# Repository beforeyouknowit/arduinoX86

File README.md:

### About ArduinoX86

I've written a blog article that gives an overview of this project and how it is used.

https://martypc.blogspot.com/2023/06/hardware-validating-emulator.html

This project was originally called Arduino8088, but then I expanded it to support the 8086, 80186, 80286, with plans for
the 80386, so it is now named the suitably generic ArduinoX86.

### Description

This project expands on the basic idea of controlling a CPU via GPIO pins to clock the CPU and read and write control
and data signals. This can be used to validate an emulator's accuracy, but also as a general method of exploring the
operation of CPU instructions and timings.

This project currently supports the following CPUs:

- CMOS variants of the 8088 (Oki, Harris 80C88, etc.)
- AMD D8088
- CMOS variants of the 8086 (Intel 80C86, Harris 80C86)
- NEC V20
- NEC V30
- Intel 80L186
- Harris 80C286
- Intel 80386EX

Where it differs from existing Raspberry Pi-based projects is that it uses an Arduino Giga for the expanded number of
GPIO pins available. The Giga has enough GPIO to operate 808X-compatible CPUs in Maximum mode. This enables several
useful signals to be read such as the QS0 & QS1 processor instruction queue status lines, which give us more insight
into the internal state of the CPU. We can also enable inputs such as READY, NMI, INTR, and TEST, so we can execute
interrupts, NMIs, emulate wait states, and potentially even simulate FPU and DMA operations.

I have been using this project to validate the cycle-accuracy of my PC
emulator, [MartyPC](https://github.com/dbalsom/martypc), and produce CPU test
suites for emulators, covering
the [8088](https://github.com/singleStepTests/8088/), [V20](https://github.com/SingleStepTests/v20)
and [8086](https://github.com/singleStepTests/8086/) and [286](https://github.com/singlesteptests/80286) to date.

This project has three main components:

- The CPU server software, which runs on the Arduino, and establishes a serial protocol to reset the CPU, load and store
  register state, as well as interactively operate the CPU if desired;
- The CPU client software, which runs on your computer and controls the CPU after the CPU server has set up initial
  register state as desired, or uploads an entire program to be run automatically with register state collected at the
  end of execution;
- The CPU socket PCB shields, which seat on top of the Arduino, and provide a physical interface between the CPU and
  GPIO
  lines.

The original "Arduino8088" project utilized an Arduino MEGA, but this board no longer supported.
It is painfully slow and limited to a serial UART instead of fast native USB communication. As of the current
release, an [Arduino Due](https://store.arduino.cc/products/arduino-due), or preferably,
an [Arduino GIGA](https://store.arduino.cc/products/giga-r1-wifi) should be used instead. A GIGA is required to
operate 5V CPUs such as older 80186's and the 80286. Despite Arduino's official warnings, the STM32 GPIO in the Giga is
5V tolerant (with a few exceptions). You will likely void your warranty and I take no responsibility for any damage to
your Arduino that occurs attempting to use a 5V CPU with your Arduino.

### 8088,8086,V20,V30 Support

Revision 1.1 of the 808X shield supports the 8086 and NEC V30 by adding a connection for the 8086's BHE pin.

The Due can operate the 8088, 8086, V20 and V30, despite these chips being 5V. The current 8088 shield feeds those CPUs
3.3V which they tolerate quite well at low clock speeds.

The Giga can operate the 8088, 8086, V20 and V30 directly at 5V if desired. The Giga requires the 3V supply pin to be
cut off the shield's pin headers and external power supplied due to the lower available overall power budget.

> [!WARNING]  
> Do not attempt to use the 8088 shield with a Giga without using external power, or you may damage your Arduino.

### 80186 Support

The ArduinoX86 cpu_server sketch supports operation of a low-voltage 80L186 on an Arduino Due.

There is no shield yet for the 80186, you will need to use a breakout board and connect directly to the Arduino Due's
headers. See [Using an 80186](https://github.com/dbalsom/arduinoX86/wiki/Using-an-80186) for more information.

### 80286 Support

A shield for the 80C286 is in the design phase, located in `/shields/286_5V`

Current support for the 80286 has been performed via breadboard.

### 80386 Support

A shield for the 80386EX CPU is provided in `/shields/386EX_V4`

## Can the CPU be clocked fast enough with an Arduino?

In short, no. We are well past the published minimum cycle times when executing programs via a serial protocol, cycle by
cycle. Some chips tolerate this better than others. When working with an Intel branded 8088, I noticed that effective
address calculations were failing to add the displacement or index register, but otherwise functioned. I have had more
luck with the AMD second-source 8088 CPUs, which seem to function perfectly under slow clocks, although they will hang
and need to be reset if not cycled for a several milliseconds. The issue is "dynamic logic" - logic gates that lose
their state if not refreshed electrically within a frequent enough interval. To be absolutely safe, it is best to use a
fully CMOS process CPU such as the 80C88. CMOS versions of most x86 chips are available.

## To use

An example application for cpu_server is provided, written in Rust, in the `/crates/exec_program` directory. It
demonstrates how to upload arbitrary code to the ArduinoX86 and display cycle traces. The client will emulate the
entire address space and set up a basic IVT.

# Project Structure

## /asm

Assembly language files, intended to be assembled with NASM. To execute code on the ArduinoX86, one must supply two
binary files, one containing the program to be executed, and one containing the register values to load onto the CPU
before program execution.

## /crates/arduinox86_client

A library crate that implements a client for the ArduinoX86's serial protocol.

## /crates/arduinox86_cpu

A library crate built on top of the `arduinox86_client` crate, this provides a `RemoteCpu` struct that models CPU state
and can execute programs.

## /crates/arduinox86_gui

A GUI (written in egui) for ArduinoX86, supporting the 386EX. It allows you to write and assemble assembly-language
programs and execute them on the CPU with an easy-to-use interface.

## /crates/exec_program

A binary implementing an interface for the `arduinox86_cpu` crate that will load a provided register state binary and
execute the specified program binary.

## /crates/test_generator

A program that generates CPU tests for emulator authors.

### /shields

Contains the KiCad project files and Gerber files for the various ArduinoX86 shields. See the README.md in each shield
directory for more information and BOMs for building each.

### /platformio/ArduinoX86

The main server code that runs on the Arduino Due or GIGA. You must have [platformio](https://platformio.org/) installed
to build and upload the project to your Arduino.

## Archived Directories

### /sketches/cpu_server

The original cpu_server Arduino IDE sketch. Development has since moved to platformio.

### /sketches/run_program

The original sketch for Arduino MEGA only demonstrating how to control an 8088. It does not contain a serial protocol
server - code is run directly from an array defined within the sketch.

# Ordering Boards

- Ordering boards from any of the KiCad projects is extremely simple using PCBWay's KiCad fabrication plugin.
  - From the Plugin and Content Manager, go the Fabrication Plugins tab, find the PCBWay plugin and install.
  - 
  - Open the PCB editor and click the PCBWay Button
  - 
  - A browser window will open to PCBWay's website with the project uploaded and acceptable defaults selected.
  - If you like you can change the board color, or get a nicer finish with gold (ENIG).
  - 
  - You can then proceed to ordering. Part of your purchase goes back to help fund the KiCad project, which is cool.
  - 

# Credits

Inspired by the Pi8088 validator created by Andreas Jonsson as part of the VirtualXT project:

https://github.com/andreas-jonsson/virtualxt/tree/develop/tools/validator/pi8088

# Other Cool Projects

- 8bitforce's Retroshield: https://www.8bitforce.com/projects/retroshield/

- homebrew8088's Raspberry Pi Hat: https://github.com/homebrew8088/pi86

- The Universal Chip Analyser (U. C. A.): https://x86.fr/uca/

- Foxtech's 486 Breadboard Computer: https://www.youtube.com/watch?v=wSiDSdHS2QQ

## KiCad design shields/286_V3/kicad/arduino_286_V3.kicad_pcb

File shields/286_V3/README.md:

## ArduinoX86 286 5V Shield

This Shield is for a 5V CMOS 286 in a PLCC-68 package, such as the Harris 80C286.

> [!WARNING]  
> This hat is to be used ONLY with the Arduino GIGA. Using this HAT with an Arduino Due will damage/destroy your
> Arduino.

> [!CAUTION]
> This hat is in development. Do not order it.

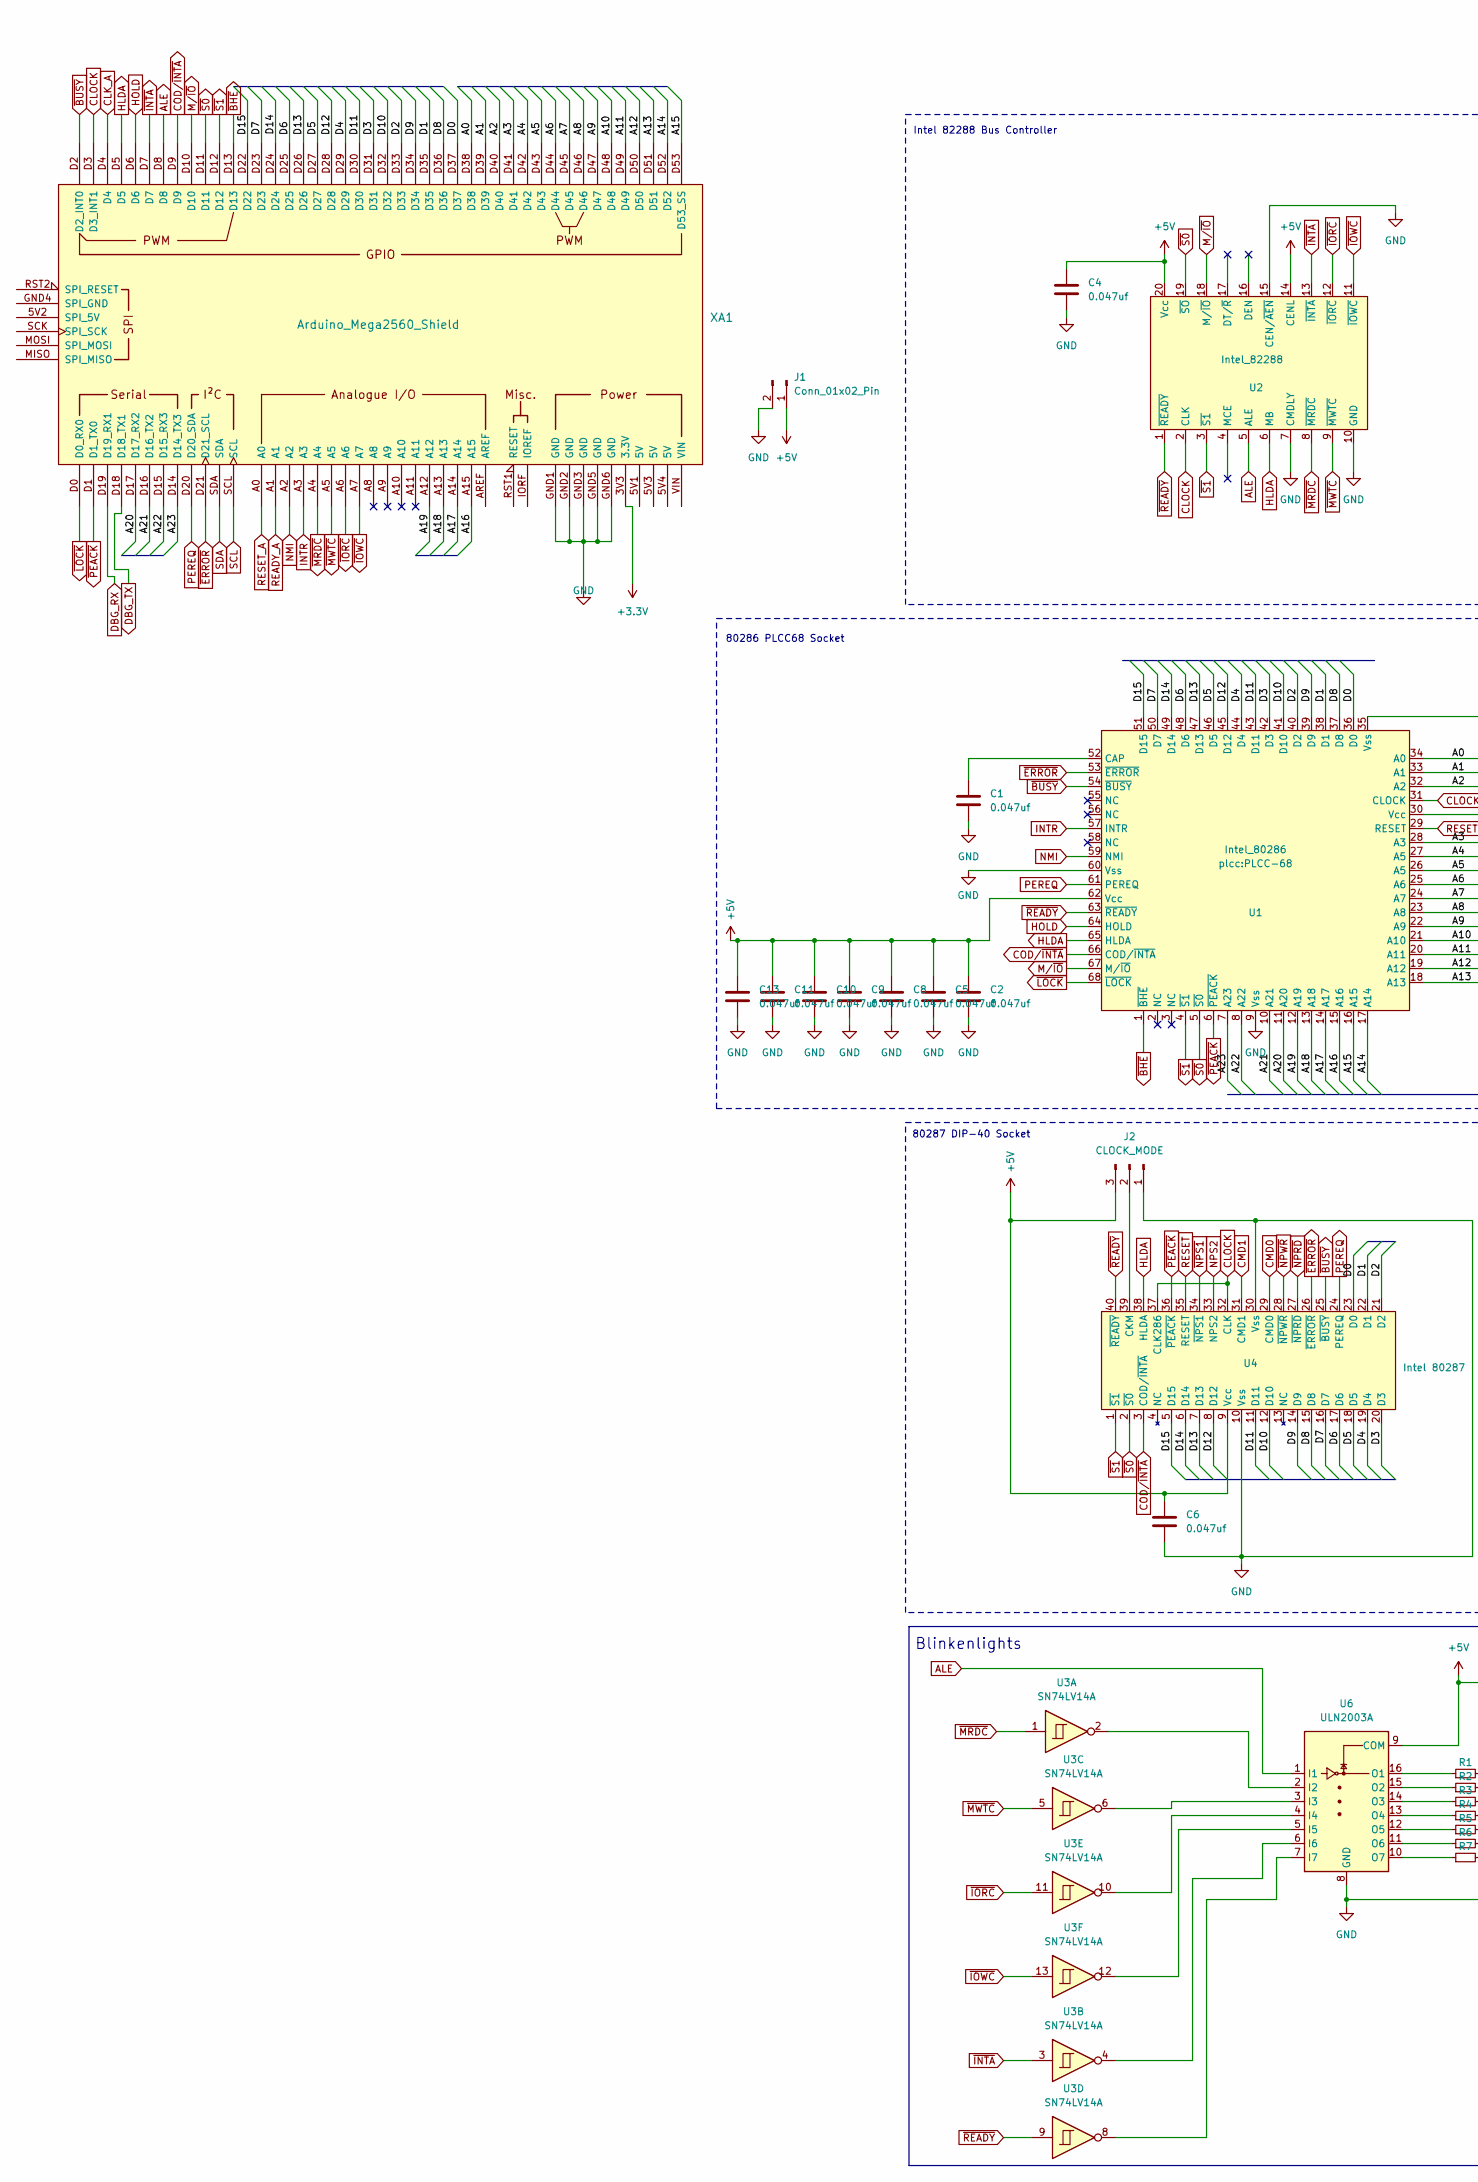
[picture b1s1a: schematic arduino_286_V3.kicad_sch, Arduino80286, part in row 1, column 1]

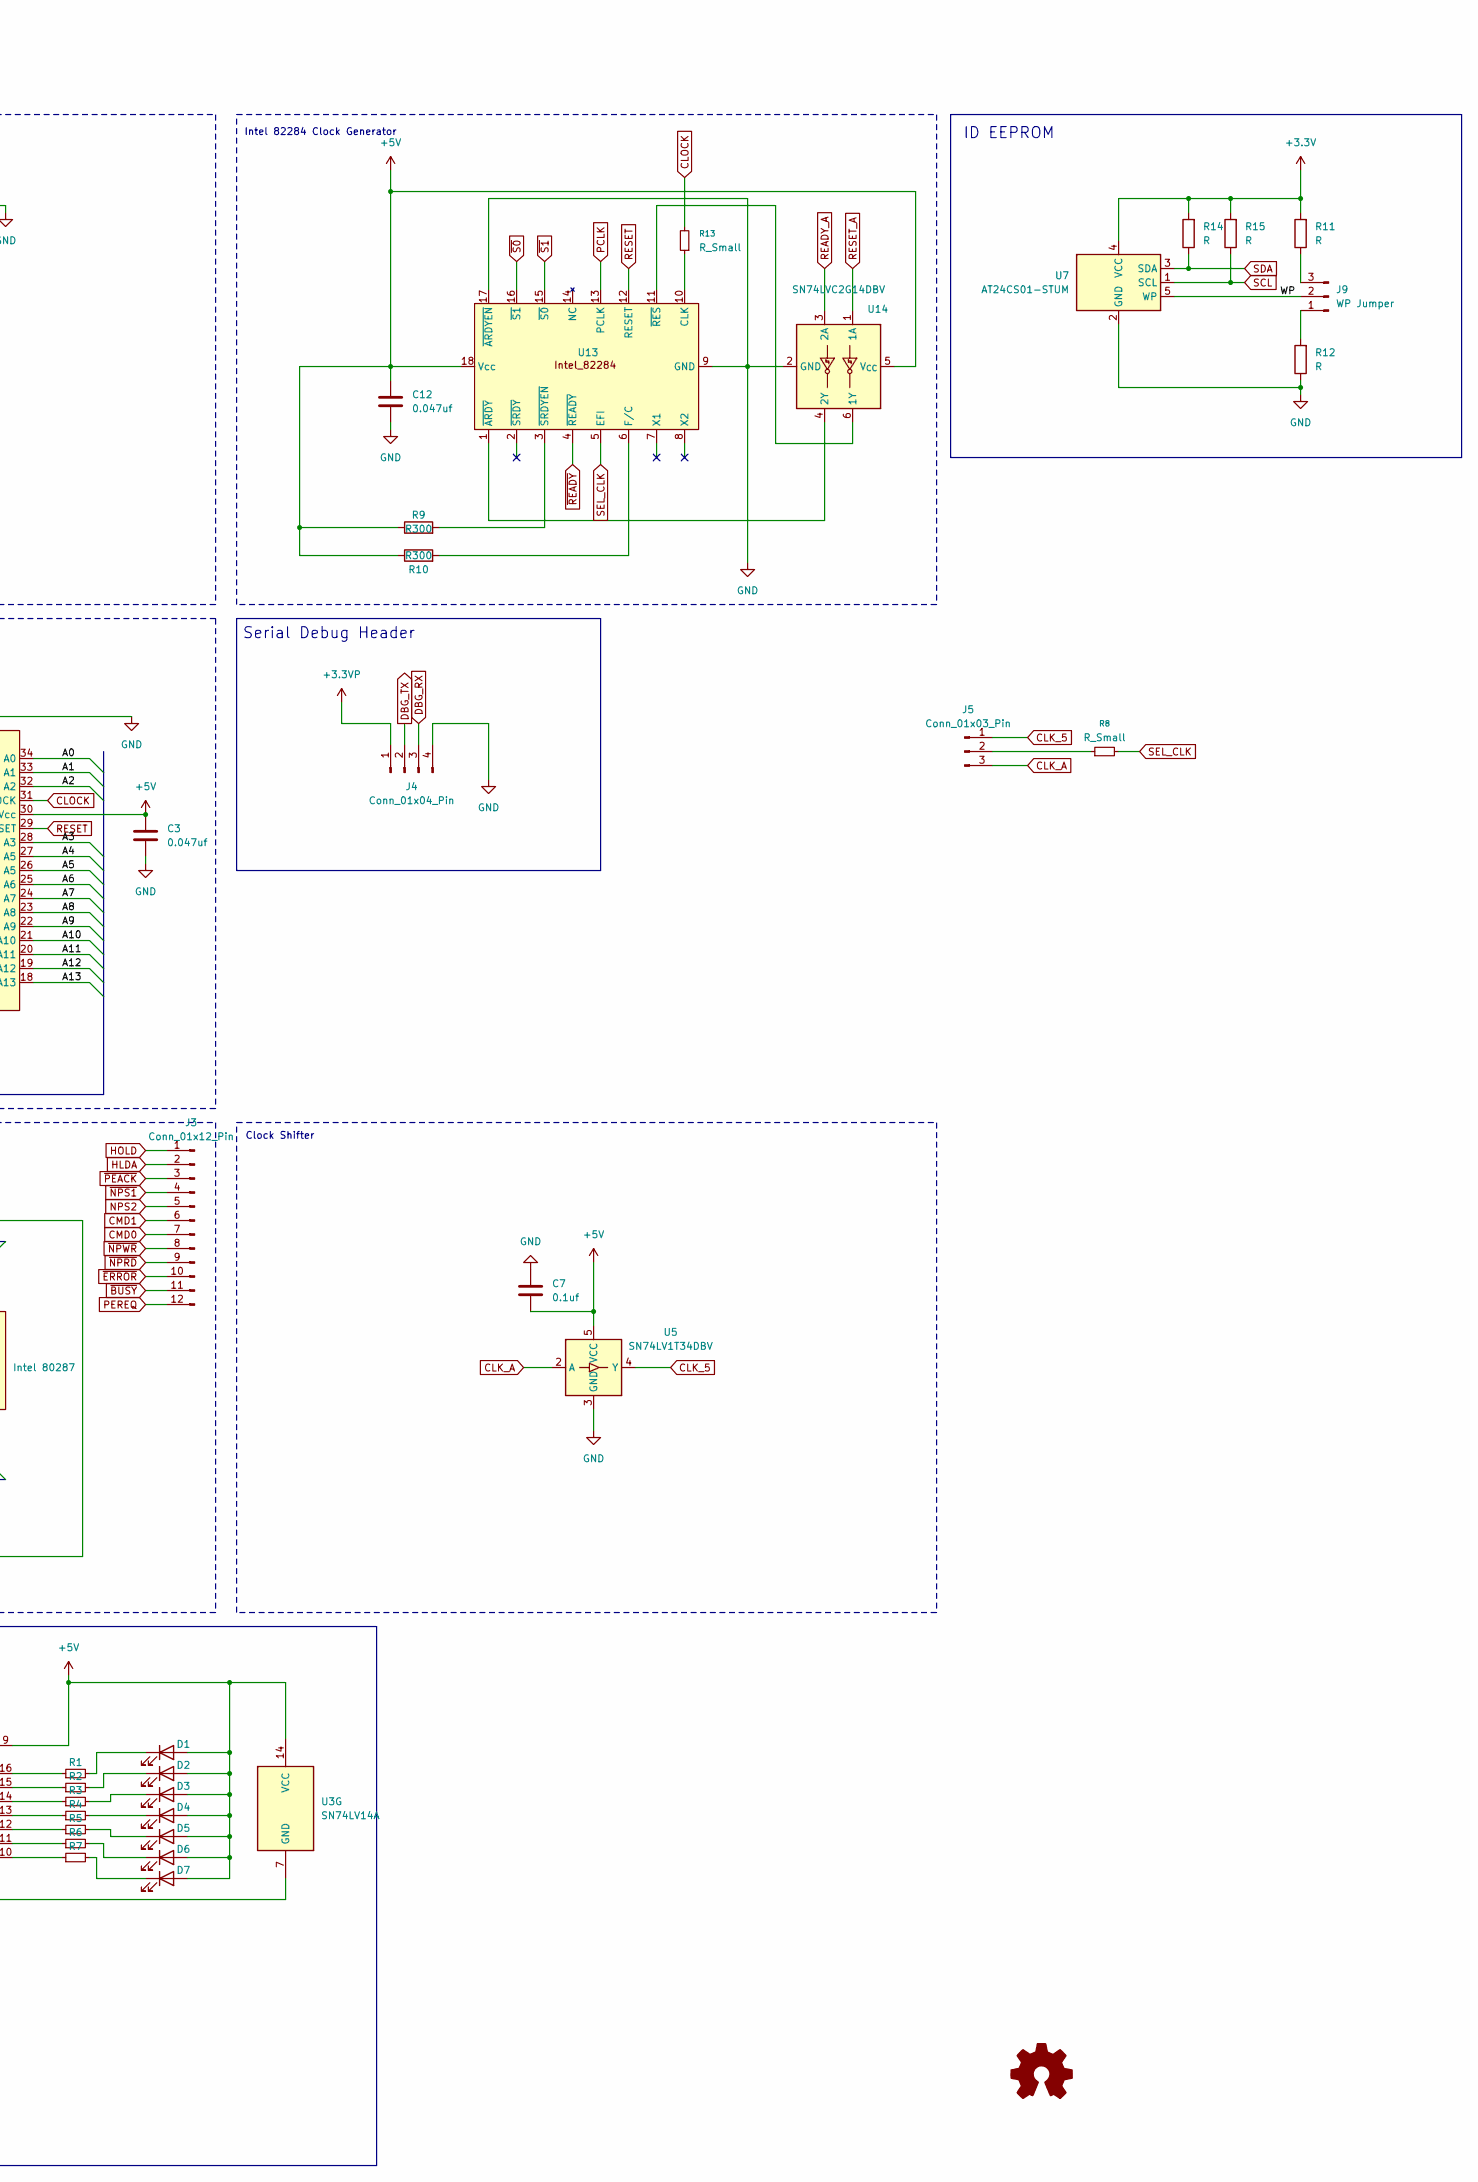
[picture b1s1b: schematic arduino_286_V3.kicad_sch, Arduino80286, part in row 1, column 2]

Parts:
C1, C2, C3, C4, C5, C6, C8, C9, C10, C11, C12, C13: 0.047uf; C_0603_1608Metric_Pad1.08x0.95mm_HandSolder
C7: 0.1uf; C_0603_1608Metric_Pad1.08x0.95mm_HandSolder
D1, D2, D3, D4, D5, D6, D7: LED; LED_0603_1608Metric_Pad1.05x0.95mm_HandSolder
J1: Conn_01x02_Pin; PinHeader_1x02_P2.54mm_Horizontal
J2: CLOCK_MODE; PinHeader_1x03_P2.54mm_Vertical
J3: Conn_01x12_Pin; PinHeader_1x12_P2.54mm_Vertical
J4: Conn_01x04_Pin; PinHeader_1x04_P2.54mm_Vertical
J5: Conn_01x03_Pin; PinHeader_1x03_P2.54mm_Vertical
J9: WP Jumper; PinHeader_1x03_P2.54mm_Vertical
R1, R2, R3, R4, R5, R6, R7, R8, R13: R_Small; R_0603_1608Metric_Pad0.98x0.95mm_HandSolder
R9, R10: R300; R_0603_1608Metric_Pad0.98x0.95mm_HandSolder
R11, R12, R14, R15: R; R_0603_1608Metric_Pad0.98x0.95mm_HandSolder
U1: Intel_80286; PLCC-68
U2: Intel_82288; DIP-20_W7.62mm_Socket
U3: SN74LV14A; TSSOP-14_4.4x5mm_P0.65mm
U4: Intel 80287; DIP-40_W15.24mm_Socket
U5: SN74LV1T34DBV; SOT-23-5
U6: ULN2003A; TSSOP-16_4.4x5mm_P0.65mm
U7: AT24CS01-STUM; SOT-23-5
U13: DIP-18_W7.62mm_Socket
U14: SN74LVC2G14DBV; SOT-23-6
XA1: Arduino_Mega2560_Shield

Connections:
+3.3V: R11.2, R14.2, R15.2, U7.4 (VCC), XA1.3V3 (3.3V); also elsewhere on the board
+3.3VP: J4.1
/A0: U1.34 (A0), XA1.D38
/A1: U1.33 (A1), XA1.D39
/A2: U1.32 (A2), XA1.D40
/A3: U1.28 (A3), XA1.D41
/A4: U1.27 (A5), XA1.D42
/A5: U1.26 (A5), XA1.D43
/A6: U1.25 (A6), XA1.D44
/A7: U1.24 (A7), XA1.D45
/A8: U1.23 (A8), XA1.D46
/A9: U1.22 (A9), XA1.D47
/A10: U1.21 (A10), XA1.D48
/A11: U1.20 (A11), XA1.D49
/A12: U1.19 (A12), XA1.D50
/A13: U1.18 (A13), XA1.D51
/A14: U1.17 (A14), XA1.D52
/A15: U1.16 (A15), XA1.D53 (D53_SS)
/A16: U1.15 (A16), XA1.A15
/A17: U1.14 (A17), XA1.A14
/A18: U1.13 (A18), XA1.A13
/A19: U1.12 (A19), XA1.A12
/A20: U1.11 (A20), XA1.D17 (D17_RX2)
/A21: U1.10 (A21), XA1.D16 (D16_TX2)
/A22: U1.8 (A22), XA1.D15 (D15_RX3)
/A23: U1.7 (A23), XA1.D14 (D14_TX3)
/D0: U1.36 (D0), U4.23 (D0), XA1.D37
/D1: U1.38 (D1), U4.22 (D1), XA1.D35
/D2: U1.40 (D2), U4.21 (D2), XA1.D33
/D3: U1.42 (D3), U4.20 (D3), XA1.D31
/D4: U1.44 (D4), U4.19 (D4), XA1.D29
/D5: U1.46 (D5), U4.18 (D5), XA1.D27
/D6: U1.48 (D6), U4.17 (D6), XA1.D25
/D7: U1.50 (D7), U4.16 (D7), XA1.D23
/D8: U1.37 (D8), U4.15 (D8), XA1.D36
/D9: U1.39 (D9), U4.14 (D9), XA1.D34
/D10: U1.41 (D10), U4.12 (D10), XA1.D32
/D11: U1.43 (D11), U4.11 (D11), XA1.D30
/D12: U1.45 (D12), U4.8 (D12), XA1.D28
/D13: U1.47 (D13), U4.7 (D13), XA1.D26
/D14: U1.49 (D14), U4.6 (D14), XA1.D24
/D15: U1.51 (D15), U4.5 (D15), XA1.D22
/WP: J9.2, U7.5 (WP)
ALE: U2.5 (ALE), U6.1 (I1), XA1.D8
CLK_5: J5.1, U5.4 (Y)
CLK_A: J5.3, U5.2 (A), XA1.D4
CLOCK: R13.2, U1.31 (CLOCK), U2.2 (CLK), U4.32 (CLK), U4.37 (CLK286), XA1.D3 (D3_INT1)
COD/~INTA: U1.66 (COD/~INTA), U4.3 (COD/~INTA), XA1.D9
DBG_RX: J4.3, XA1.D19 (D19_RX1)
DBG_TX: J4.2, XA1.D18 (D18_TX1)
HLDA: J3.2, U1.65 (HLDA), U2.6 (MB), U4.38 (HLDA), XA1.D5
HOLD: J3.1, U1.64 (HOLD), XA1.D6
INTR: U1.57 (INTR), XA1.A3
M/~IO: U1.67 (M/~IO), U2.18 (M/~IO), XA1.D10
NMI: U1.59 (NMI), XA1.A2
unnamed: D1.1 (K), R1.2
unnamed: D2.1 (K), R2.2
unnamed: D3.1 (K), R3.2
unnamed: D4.1 (K), R4.2
unnamed: D5.1 (K), R5.2
unnamed: D7.1 (K), R7.2
unnamed: J2.2, U4.39 (CKM)
unnamed: J3.4, U4.34 (~NPS1)
unnamed: J3.5, U4.33 (NPS2)
unnamed: J3.6, U4.31 (CMD1)
unnamed: J3.7, U4.29 (CMD0)
unnamed: J3.8, U4.28 (~NPWR)
unnamed: J3.9, U4.27 (~NPRD)
unnamed: J5.2, R8.1
unnamed: J9.1, R12.2
unnamed: J9.3, R11.1
unnamed: C1.2, U1.52 (CAP)
unnamed: U3.2, U6.2 (I2)
unnamed: U3.6, U6.3 (I3)
unnamed: U3.10, U6.4 (I4)
unnamed: U3.12, U6.5 (I5)
unnamed: U3.4, U6.6 (I6)
unnamed: U3.8, U6.7 (I7)
unnamed: R1.1, U6.16 (O1)
unnamed: R2.1, U6.15 (O2)
unnamed: R3.1, U6.14 (O3)
unnamed: R4.1, U6.13 (O4)
unnamed: R5.1, U6.12 (O5)
unnamed: R6.1, U6.11 (O6)
unnamed: R7.1, U6.10 (O7)
unnamed: R13.1, U13.10 (CLK)
unnamed: R10.2, U13.6 (F/C)
unnamed: U13.1 (~ARDY), U14.4 (2Y)
unnamed: U13.11 (~RES), U14.6 (1Y)
unnamed: R9.2, U13.3 (~SRDYEN)
PCLK: U13.13 (PCLK)
PEREQ: J3.12, U1.61 (PEREQ), U4.24 (PEREQ), XA1.D20 (D20_SDA)
READY_A: U14.3 (2A), XA1.A1
RESET: U1.29 (RESET), U4.35 (RESET), U13.12 (RESET)
RESET_A: U14.1 (1A), XA1.A0
SCL: R15.1, U7.1 (SCL), XA1.SCL
SDA: R14.1, U7.3 (SDA), XA1.SDA
SEL_CLK: R8.2, U13.5 (EFI)
~BHE: U1.1 (~BHE), XA1.D13
~BUSY: J3.11, U1.54 (~BUSY), U4.25 (~BUSY), XA1.D2 (D2_INT0)
~ERROR: J3.10, U1.53 (~ERROR), U4.26 (~ERROR), XA1.D21 (D21_SCL)
~INTA: U2.13 (~INTA), U3.3, XA1.D7
~IORC: U2.12 (~IORC), U3.11, XA1.A6
~IOWC: U2.11 (~IOWC), U3.13, XA1.A7
~LOCK: U1.68 (~LOCK), XA1.D0 (D0_RX0)
~MRDC: U2.8 (~MRDC), U3.1, XA1.A4
~MWTC: U2.9 (~MWTC), U3.5, XA1.A5
~PEACK: J3.3, U1.6 (~PEACK), U4.36 (~PEACK), XA1.D1 (D1_TX0)
~READY: U1.63 (~READY), U2.1 (~READY), U3.9, U4.40 (~READY), U13.4 (~READY)
~S0: U1.5 (~S0), U2.19 (~SO), U4.2 (~S0), U13.16 (~S1), XA1.D11
~S1: U1.4 (~S1), U2.3 (~S1), U4.1 (~S1), U13.15 (~S0), XA1.D12

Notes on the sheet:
Blinkenlights
ID EEPROM
Intel 82284 Clock Generator
Clock Shifter
Intel 82288 Bus Controller
80286 PLCC68 Socket
80287 DIP-40 Socket
Serial Debug Header

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
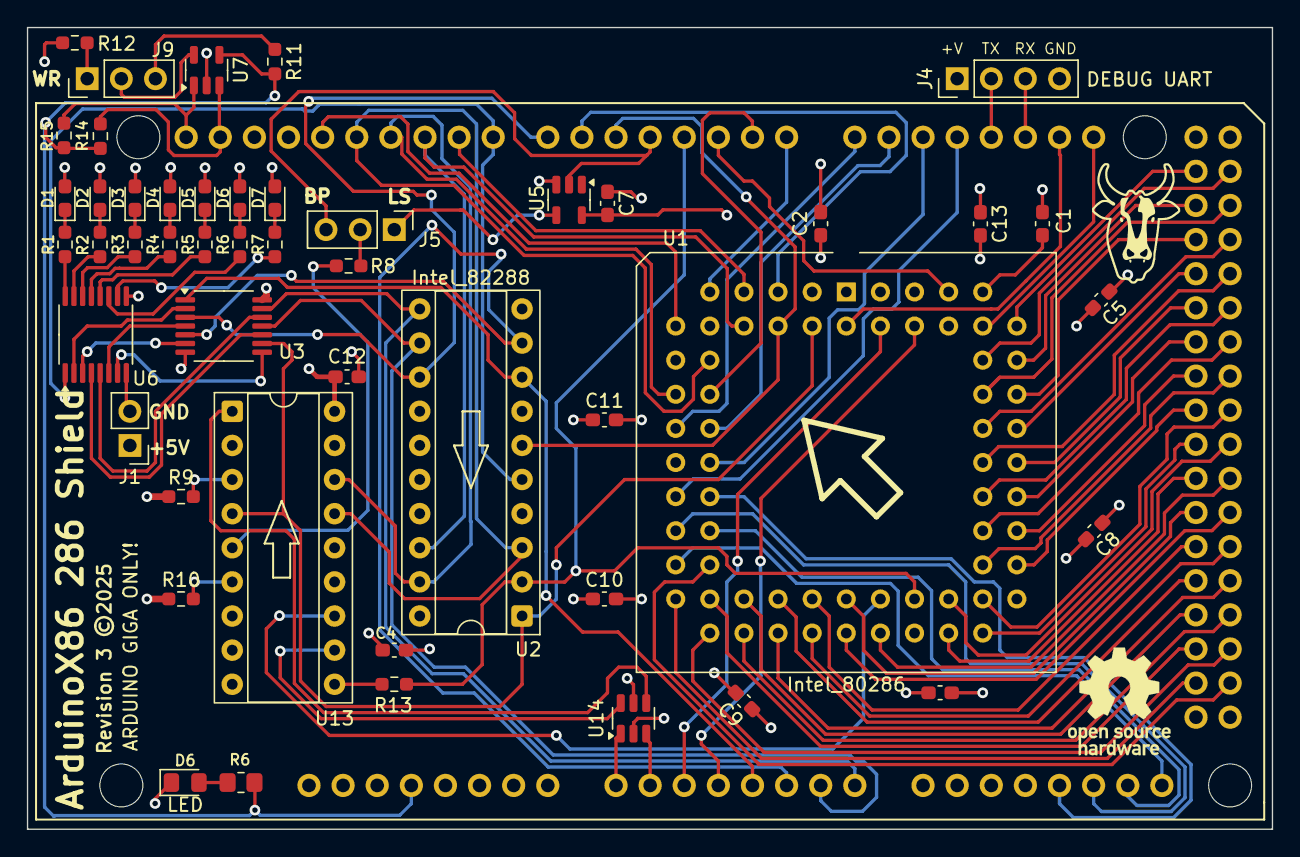
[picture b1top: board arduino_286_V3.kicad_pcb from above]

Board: 4 copper layers, 92.7 x 59.7 mm, 49 parts (0 on the bottom side), 106 nets.

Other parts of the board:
D6#2: LED; LED_0603_1608Metric_Pad1.05x0.95mm_HandSolder
R6#2: 750Ω; R_0805_2012Metric_Pad1.20x1.40mm_HandSolder

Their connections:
+3.3V: R6#2.1; also elsewhere on the board

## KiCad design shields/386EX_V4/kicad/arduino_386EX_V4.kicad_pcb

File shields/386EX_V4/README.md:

## ArduinoX86 386EX Shield V4

This is the latest shield design for the 386EX CPU. It supports the addition of a 387SX FPU via stacking headers.
The 386EX is a low-voltage variant of the 386 with a 16-bit data bus, intended for embedded applications.

This shield has external power pins. You may connect a 3.3V or 5V power source to the pins. I recommend using Dupont
connectors.

You may find that the CPU runs even without external power. This is due to the CMOS process - many CMOS CPUs can power
themselves by sinking current from any input pin. Correct operation in this state is not guaranteed.

This shield should be compatible with the Arduino Due and GIGA. If using a Due, do not supply more than 3.3V to the
external power pins, or you will damage your Arduino Due.

Unsoldered new-old-stock 386EX chips are often available on eBay. If using a donor board, a hot plate or hot-air
station will be necessary to successfully remove the CPU without damage.

This shield adds new features over the original:

- PEREQ and ERROR pins have been connected to support stacking a 387SX
- The SMI and SMIACT pins have been connected
- The JTAG ports have been run out to a 2x4 header
- The first Asynchronous serial port has been run out to a 2x5 header (Serial0)
- The first 8 external INTR lines (INTR0-INTR7) have been run out to separate 1x4 headers
- 7 status LEDs have been added that will report the status of SMIACT, ADS, RD, WR, W/R, C/M and M/IO.

Improvements over the previous design include:

- Series termination resistor on the clock line
- Optional filter caps on the external power connector
- Larger Schmitt-triggered inverter chip to invert the D/C and M/IO LED logic states
- Test probe pads for the clock line near the CPU
- I2C EEPROM for automatic board identification and write-protect jumper

> [!WARNING]  
> Successfully assembling this board requires advanced soldering skills. A solder mask, paste and hot plate are
> recommended, or solid experience in drag-soldering techniques.

## BOM

- TBD

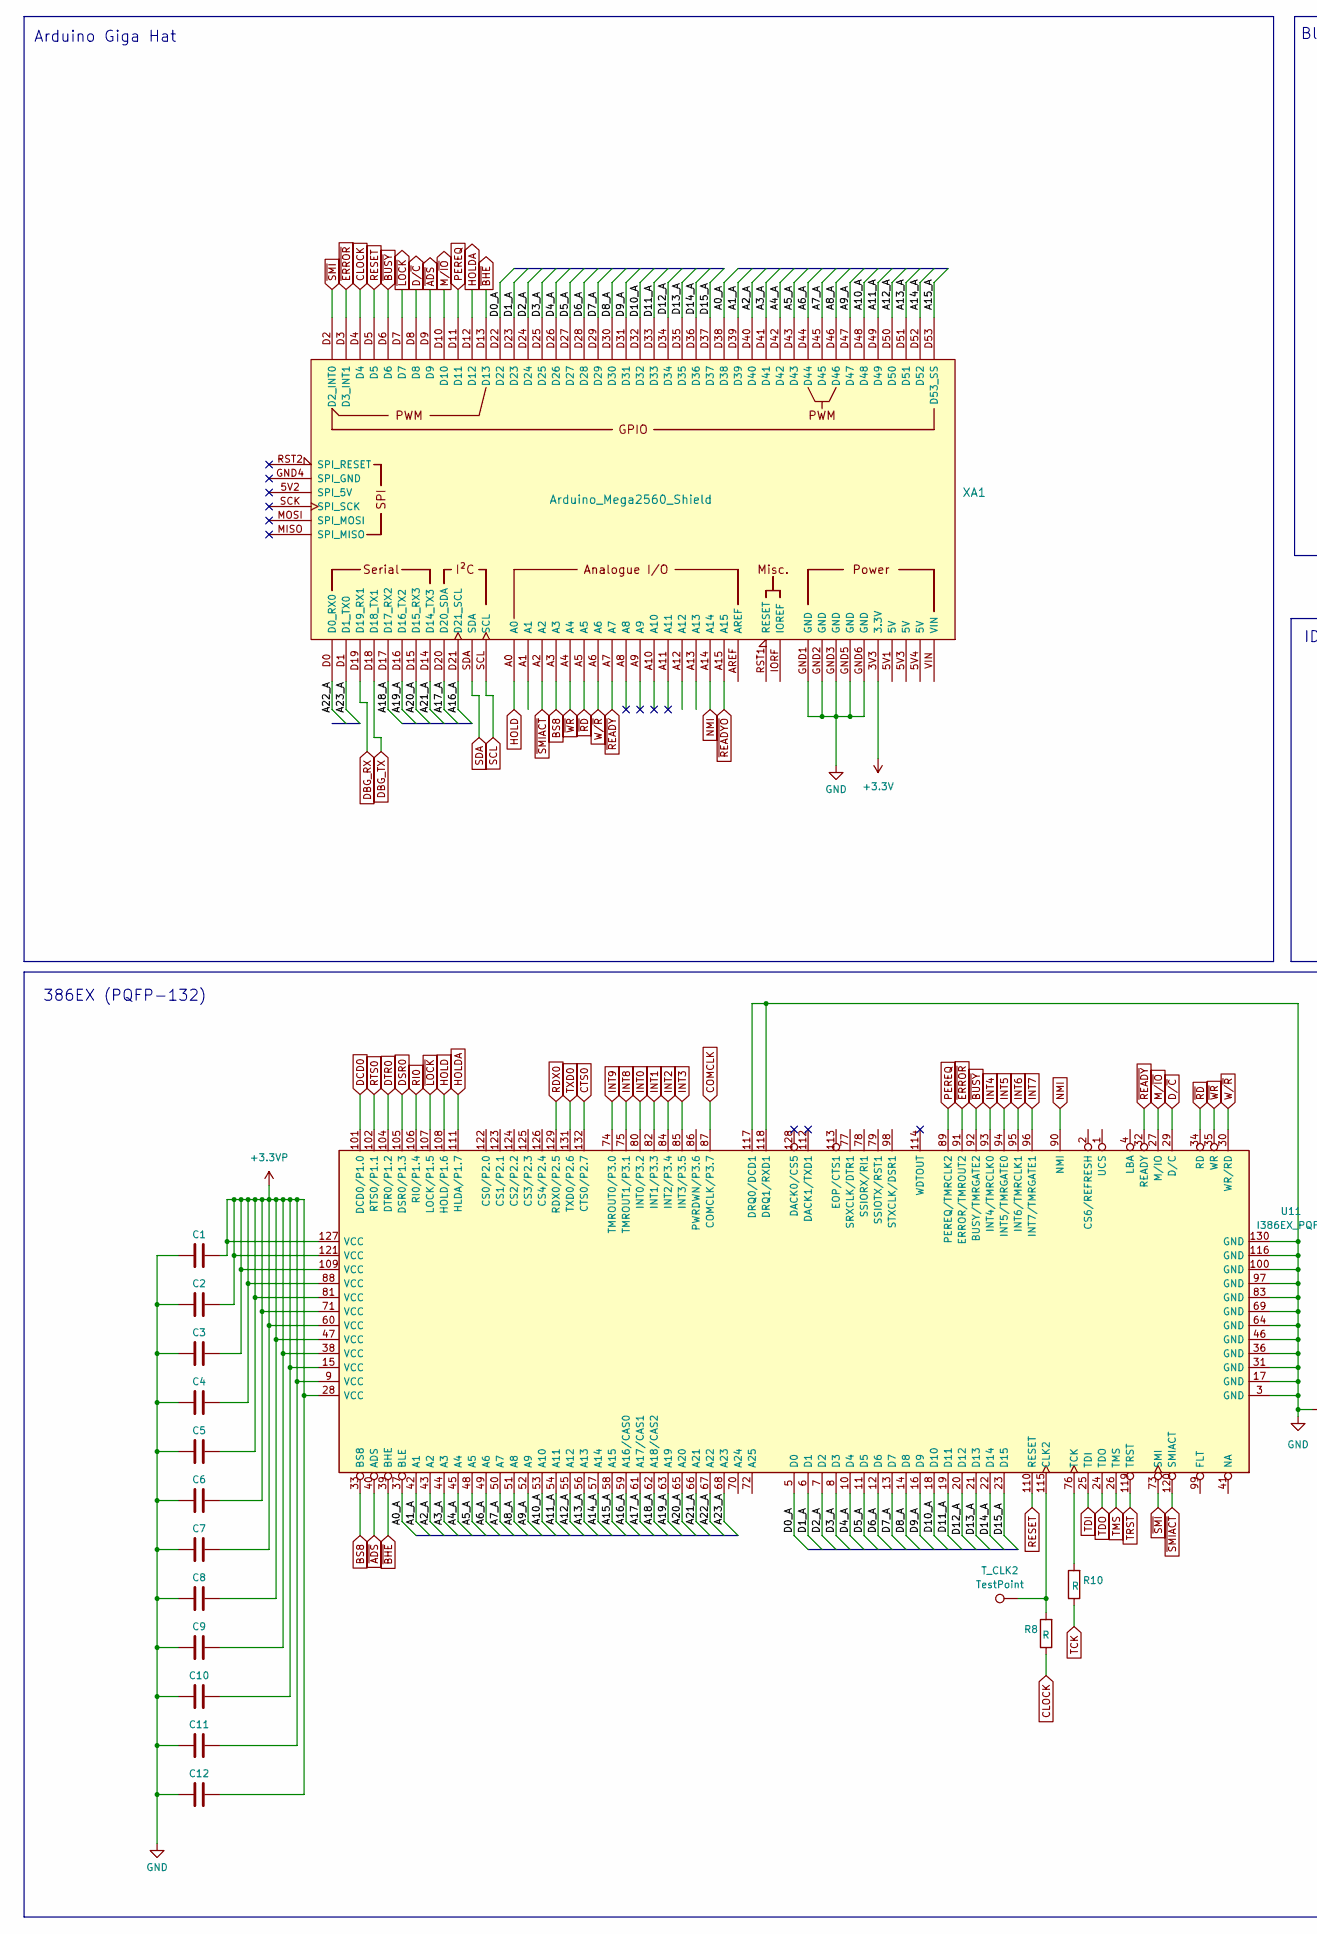
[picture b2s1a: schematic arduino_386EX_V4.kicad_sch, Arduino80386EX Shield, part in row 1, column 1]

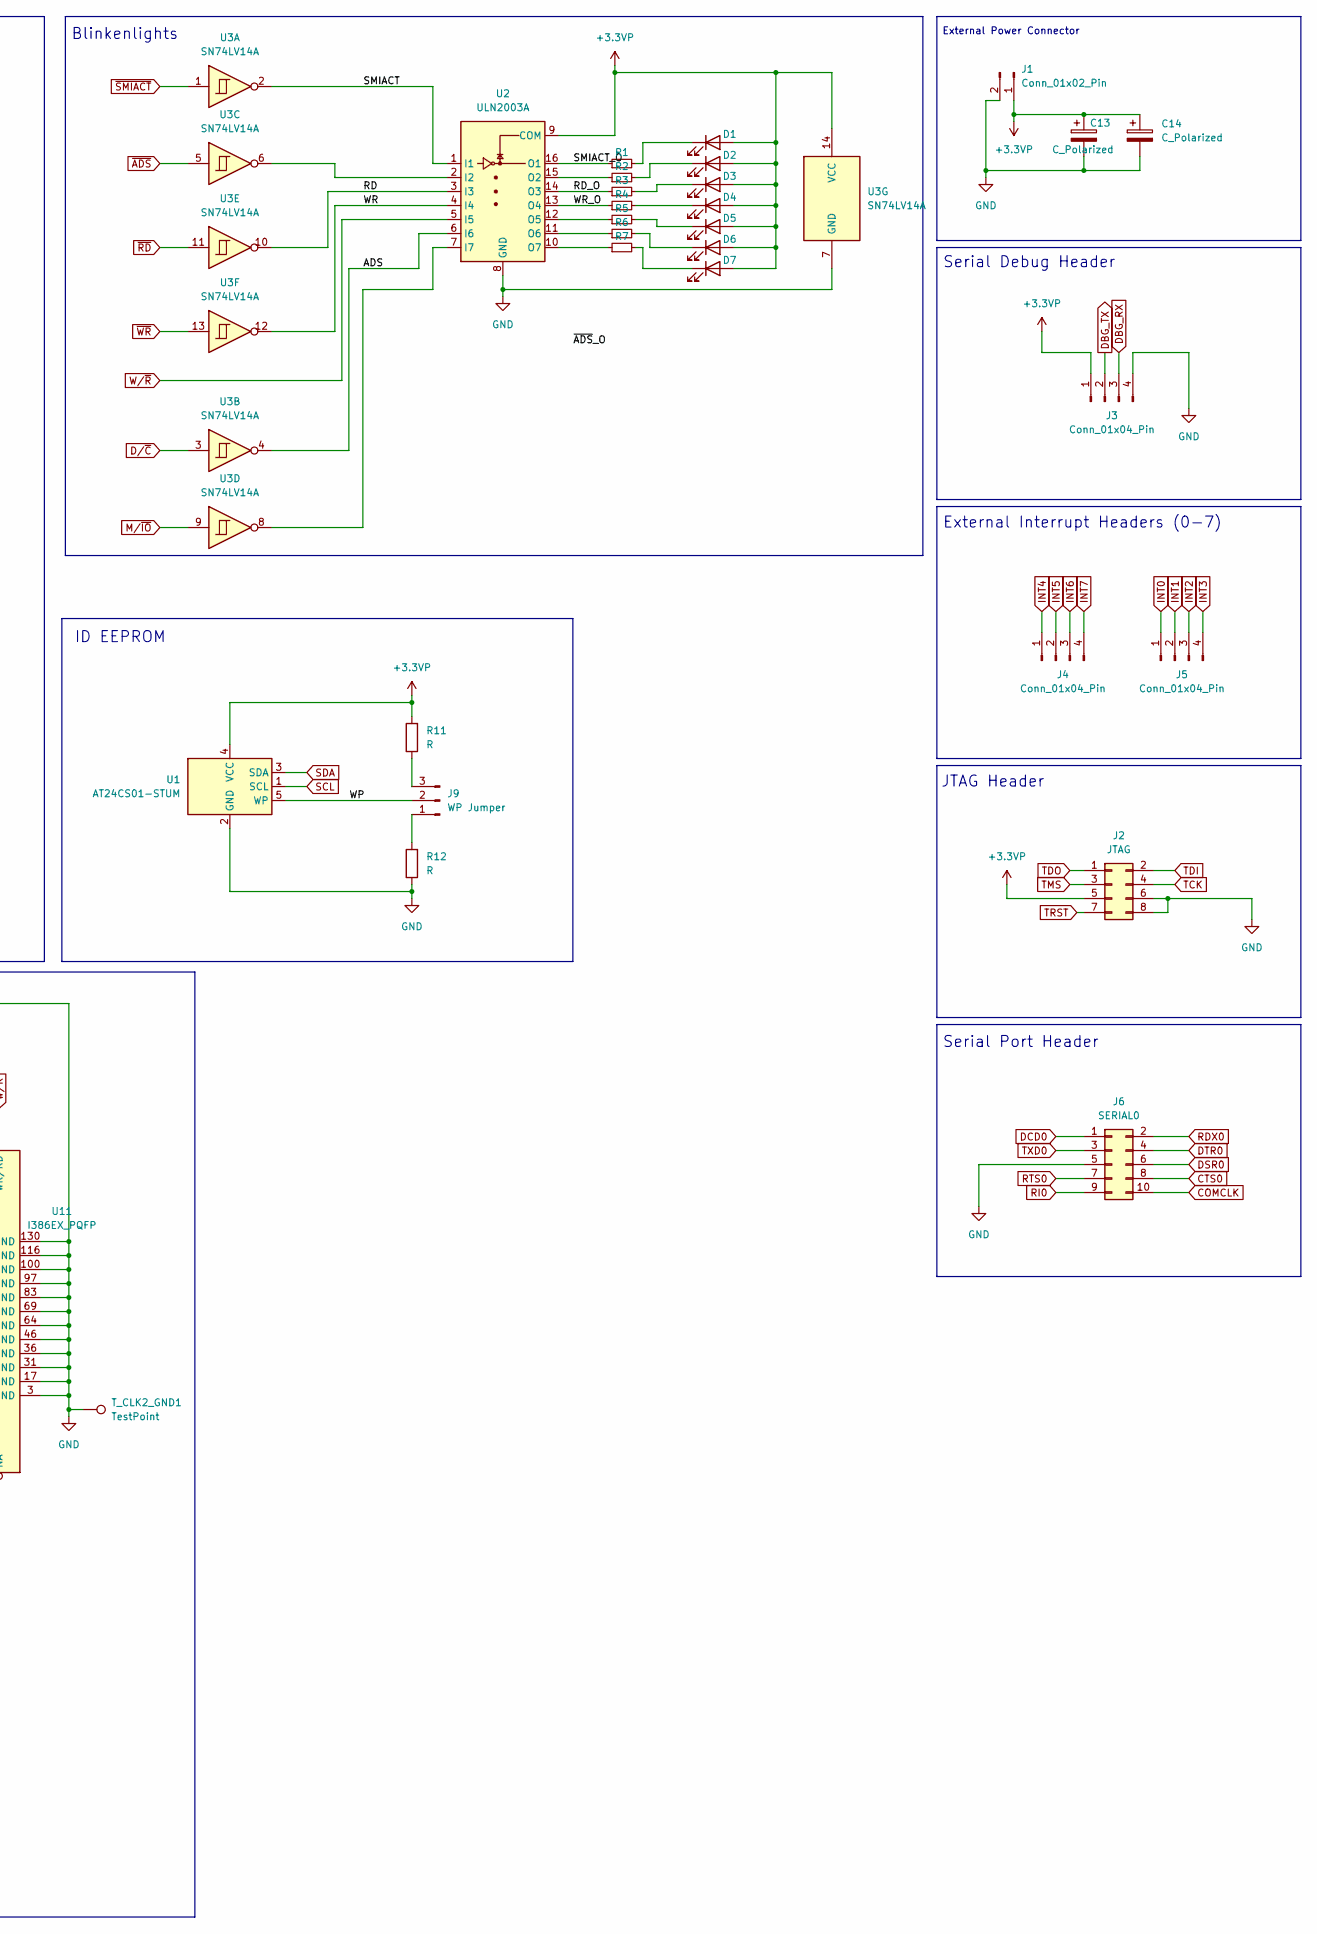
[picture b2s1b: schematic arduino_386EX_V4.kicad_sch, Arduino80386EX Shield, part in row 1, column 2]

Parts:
C1, C2, C3, C4, C5, C6, C7, C8, C9, C10, C11, C12: C; C_0603_1608Metric_Pad1.08x0.95mm_HandSolder
C13: C_Polarized; C_Radial_D4.0mm_H5.0mm_P1.50mm
C14: C_Polarized; C_Disc_D5.0mm_W2.5mm_P2.50mm
D1, D2, D3, D4, D5, D6, D7: LED; LED_0603_1608Metric_Pad1.05x0.95mm_HandSolder
J1: Conn_01x02_Pin; PinHeader_1x02_P2.54mm_Horizontal
J2: JTAG; PinHeader_2x04_P2.54mm_Vertical
J3, J4, J5: Conn_01x04_Pin; PinHeader_1x04_P2.54mm_Vertical
J6: SERIAL0; PinHeader_2x05_P2.54mm_Vertical
J9: WP Jumper; PinHeader_1x03_P2.54mm_Vertical
R1, R2, R3, R4, R5, R6, R7: R_Small; R_0603_1608Metric_Pad0.98x0.95mm_HandSolder
R8, R10, R11, R12: R; R_0603_1608Metric_Pad0.98x0.95mm_HandSolder
T_CLK2, T_CLK2_GND1: TestPoint; TestPoint_Pad_D1.0mm
U1: AT24CS01-STUM; SOT-23-5
U2: ULN2003A; TSSOP-16_4.4x5mm_P0.65mm
U3: SN74LV14A; TSSOP-14_4.4x5mm_P0.65mm
U11: I386EX_PQFP; PQFP-132_24x24mm_P0.635mm_i386
XA1: Arduino_Mega2560_Shield

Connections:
/A0_A: U11.37 (BLE), XA1.D38
/A1_A: U11.42 (A1), XA1.D39
/A2_A: U11.43 (A2), XA1.D40
/A3_A: U11.44 (A3), XA1.D41
/A4_A: U11.45 (A4), XA1.D42
/A5_A: U11.48 (A5), XA1.D43
/A6_A: U11.49 (A6), XA1.D44
/A7_A: U11.50 (A7), XA1.D45
/A8_A: U11.51 (A8), XA1.D46
/A9_A: U11.52 (A9), XA1.D47
/A10_A: U11.53 (A10), XA1.D48
/A11_A: U11.54 (A11), XA1.D49
/A12_A: U11.55 (A12), XA1.D50
/A13_A: U11.56 (A13), XA1.D51
/A14_A: U11.57 (A14), XA1.D52
/A15_A: U11.58 (A15), XA1.D53 (D53_SS)
/A16_A: U11.59 (A16/CAS0), XA1.D21 (D21_SCL)
/A17_A: U11.61 (A17/CAS1), XA1.D20 (D20_SDA)
/A18_A: U11.62 (A18/CAS2), XA1.D17 (D17_RX2)
/A19_A: U11.63 (A19), XA1.D16 (D16_TX2)
/A20_A: U11.65 (A20), XA1.D15 (D15_RX3)
/A21_A: U11.66 (A21), XA1.D14 (D14_TX3)
/A22_A: U11.67 (A22), XA1.D0 (D0_RX0)
/A23_A: U11.68 (A23), XA1.D1 (D1_TX0)
/ADS: U2.6 (I6), U3.4
/D0_A: U11.5 (D0), XA1.D22
/D1_A: U11.6 (D1), XA1.D23
/D2_A: U11.7 (D2), XA1.D24
/D3_A: U11.8 (D3), XA1.D25
/D4_A: U11.10 (D4), XA1.D26
/D5_A: U11.11 (D5), XA1.D27
/D6_A: U11.12 (D6), XA1.D28
/D7_A: U11.13 (D7), XA1.D29
/D8_A: U11.14 (D8), XA1.D30
/D9_A: U11.16 (D9), XA1.D31
/D10_A: U11.18 (D10), XA1.D32
/D11_A: U11.19 (D11), XA1.D33
/D12_A: U11.20 (D12), XA1.D34
/D13_A: U11.21 (D13), XA1.D35
/D14_A: U11.22 (D14), XA1.D36
/D15_A: U11.23 (D15), XA1.D37
/RD: U2.3 (I3), U3.10
/RD_O: R3.1, U2.14 (O3)
/SMIACT: U2.1 (I1), U3.2
/SMIACT_O: R1.1, U2.16 (O1)
/WP: J9.2, U1.5 (WP)
/WR: U2.4 (I4), U3.12
/WR_O: R4.1, U2.13 (O4)
BS8: U11.33 (BS8), XA1.A3
CLOCK: R8.1, XA1.D4
COMCLK: J6.10, U11.87 (COMCLK/P3.7)
CTS0: J6.8, U11.132 (CTS0/P2.7)
DBG_RX: J3.3, XA1.D19 (D19_RX1)
DBG_TX: J3.2, XA1.D18 (D18_TX1)
DCD0: J6.1, U11.101 (DCD0/P1.0)
DSR0: J6.6, U11.105 (DSR0/P1.3)
DTR0: J6.4, U11.104 (DTR0/P1.2)
D/~C: U3.3, U11.29 (D/C), XA1.D8
GND: C1.1, C2.1, C3.1, C4.1, C5.1, C6.1, C7.1, C8.1, C9.1, C10.1, C11.1, C12.1, C13.2, C14.2, J1.2, J2.6, J2.8, J3.4, J6.5, R12.1, T_CLK2_GND1.1, U1.2 (GND), U2.8 (GND), U3.7 (GND), U11.3 (GND), U11.17 (GND), U11.31 (GND), U11.36 (GND), U11.46 (GND), U11.64 (GND), U11.69 (GND), U11.83 (GND), U11.97 (GND), U11.100 (GND), U11.116 (GND), U11.117 (DRQ0/DCD1), U11.118 (DRQ1/RXD1), U11.130 (GND), XA1.GND1 (GND), XA1.GND2 (GND), XA1.GND3 (GND), XA1.GND5 (GND), XA1.GND6 (GND); also elsewhere on the board
HOLD: U11.108 (HOLD/P1.6), XA1.A0
HOLDA: U11.111 (HLDA/P1.7), XA1.D12
INT0: J5.1, U11.80 (INT0/P3.2)
INT1: J5.2, U11.82 (INT1/P3.3)
INT2: J5.3, U11.84 (INT2/P3.4)
INT3: J5.4, U11.85 (INT3/P3.5)
INT4: J4.1, U11.93 (INT4/TMRCLK0)
INT5: J4.2, U11.94 (INT5/TMRGATE0)
INT6: J4.3, U11.95 (INT6/TMRCLK1)
INT7: J4.4, U11.96 (INT7/TMRGATE1)
INT8: U11.75 (TMROUT1/P3.1)
INT9: U11.74 (TMROUT0/P3.0)
M/~IO: U3.9, U11.27 (M/IO), XA1.D10
NMI: U11.90 (NMI), XA1.A14
unnamed: D1.1 (K), R1.2
unnamed: D2.1 (K), R2.2
unnamed: D3.1 (K), R3.2
unnamed: D4.1 (K), R4.2
unnamed: D5.1 (K), R5.2
unnamed: D7.1 (K), R7.2
unnamed: J9.1, R12.2
unnamed: J9.3, R11.1
unnamed: U2.2 (I2), U3.6
unnamed: U2.7 (I7), U3.8
unnamed: R2.1, U2.15 (O2)
unnamed: R5.1, U2.12 (O5)
unnamed: R7.1, U2.10 (O7)
unnamed: R8.2, T_CLK2.1, U11.115 (CLK2)
unnamed: R10.2, U11.76 (TCK)
PEREQ: U11.89 (PEREQ/TMRCLK2), XA1.D11
RDX0: J6.2, U11.129 (RDX0/P2.5)
RESET: U11.110 (RESET), XA1.D5
RI0: J6.9, U11.106 (RI0/P1.4)
RTS0: J6.7, U11.102 (RTS0/P1.1)
SCL: U1.1 (SCL), XA1.SCL; also elsewhere on the board
SDA: U1.3 (SDA), XA1.SDA; also elsewhere on the board
TCK: J2.4, R10.1
TDI: J2.2, U11.25 (TDI)
TDO: J2.1, U11.24 (TDO)
TMS: J2.3, U11.26 (TMS)
TRST: J2.7, U11.119 (TRST)
TXD0: J6.3, U11.131 (TXD0/P2.6)
W/~R: U2.5 (I5), U11.30 (WR/RD), XA1.A6
~ADS: U3.5, U11.40 (ADS), XA1.D9
~BHE: U11.39 (BHE), XA1.D13
~BUSY: U11.92 (BUSY/TMRGATE2), XA1.D6; also elsewhere on the board
~ERROR: U11.91 (ERROR/TMROUT2), XA1.D3 (D3_INT1); also elsewhere on the board
~LOCK: U11.107 (LOCK/P1.5), XA1.D7
~RD: U3.11, U11.34 (RD), XA1.A5
~READYO: XA1.A15
~READY: U11.32 (READY), XA1.A7
~SMIACT: U3.1, U11.120 (SMIACT), XA1.A2
~SMI: U11.73 (SMI), XA1.D2 (D2_INT0)
~WR: U3.13, U11.35 (WR), XA1.A4

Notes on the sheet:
Serial Port Header
JTAG Header
Blinkenlights
ID EEPROM
External Power Connector
Serial Debug Header
External Interrupt Headers (0-7)
386EX (PQFP-132)
Arduino Giga Hat

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

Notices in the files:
platformio/ArduinoX86/src/main.cpp:
ArduinoX86 Copyright 2022-2025 Daniel Balsom
shields/286_5V/kicad/arduino_286_5V.kicad_pcb:
Revision 2 ©2025
shields/286_V3/kicad/arduino_286_V3.kicad_pcb:
Revision 3 ©2025
shields/386EX_V4/kicad/arduino_386EX_V4.kicad_pcb:
Revision 4.1 ©2025
shields/387SX_V2/kicad/arduino_387SX_V2.kicad_pcb:
Revision 3.0 ©2025
shields/80186/kicad/arduino_80186.kicad_pcb:
©2025 Revision 1.0
